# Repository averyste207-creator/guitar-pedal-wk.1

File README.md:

# Distortion Pedal

A DIY guitar distortion pedal project. This repository contains the circuit schematic and can be used to document the design, build process, testing, and future revisions.

## Circuit Schematic

## Overview

The schematic shows an analog distortion circuit built around an **LM741 operational amplifier**, with diode-clipping stages and adjustable controls.

- **Input:** Guitar signal input
- **Amplifier:** LM741 op-amp stage
- **Clipping:** Diodes provide signal clipping for distortion
- **Controls:** Potentiometers for adjusting the circuit response
- **Power:** 9 V supply is shown in the schematic
- **Output:** Distorted signal output

> This description is based on the current schematic. Confirm component values, pin connections, and power requirements before building the circuit.

## Components

The schematic includes the following parts (check the drawing and your chosen component footprints before ordering):

- LM741 operational amplifier
- 1N34A and 1N4148 diodes
- Resistors and capacitors as labeled in the schematic
- Potentiometers RV1 and RV2
- Input and output jacks
- 9 V power connection
- Breadboard or suitable PCB, hookup wire, and enclosure hardware

## Build Notes

1. Verify the schematic and component values.
2. Assemble the circuit on a breadboard before making a permanent PCB.
3. Check the power and ground connections before applying power.
4. Test with a low-volume amplifier setting first, then adjust the controls.
5. Record any changes to component values or wiring in this README.

## Project Status

**Status:** Schematic / prototype stage.

Build instructions, audio samples, enclosure details, and PCB files can be added as the project develops.

## Safety and Disclaimer

This is a low-voltage electronics project, but incorrect wiring can damage components or connected equipment. Double-check the power polarity and op-amp pinout before powering the circuit.

## License

No license has been specified yet. Add a `LICENSE` file if you want to define how others may use, modify, and distribute this project.

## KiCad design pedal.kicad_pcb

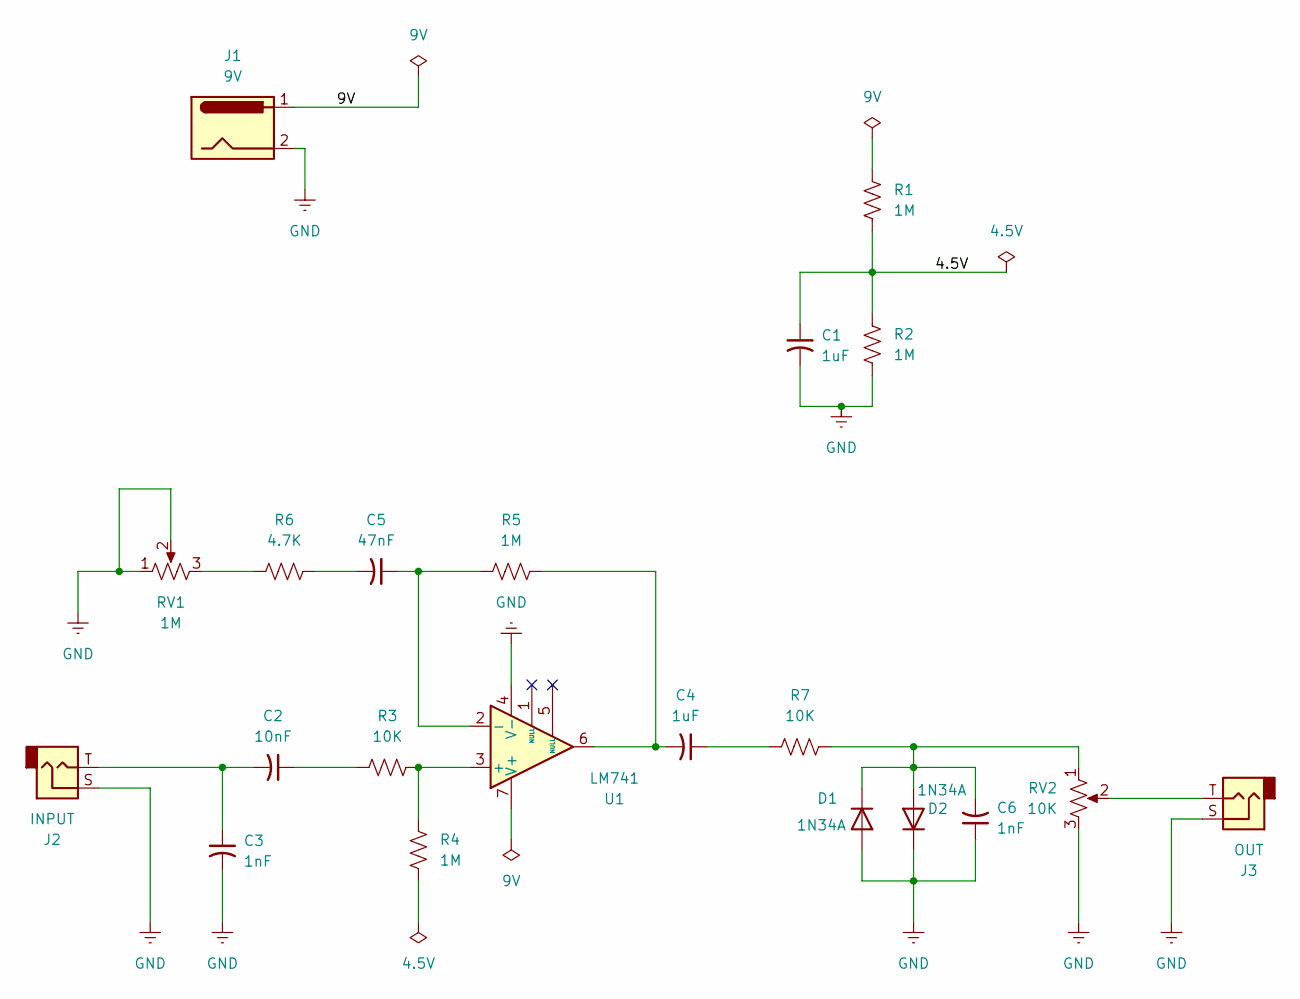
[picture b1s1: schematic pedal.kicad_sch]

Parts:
C1, C4: 1uF; CP_Radial_D4.0mm_P1.50mm
C2: 10nF; CP_Radial_D4.0mm_P1.50mm
C3, C6: 1nF; CP_Radial_D4.0mm_P1.50mm
C5: 47nF; CP_Radial_D4.0mm_P1.50mm
D1, D2: 1N34A; D_DO-35_SOD27_P7.62mm_Horizontal
J1: 9V; BarrelJack_Wuerth_694108106102_2.5x5.5mm
J2: INPUT; Jack_6.35mm_Neutrik_NMJ4HCD2_Horizontal
J3: OUT; Jack_6.35mm_Neutrik_NMJ4HCD2_Horizontal
R1, R2, R4, R5: 1M; R_Axial_DIN0204_L3.6mm_D1.6mm_P5.08mm_Horizontal
R3, R7: 10K; R_Axial_DIN0204_L3.6mm_D1.6mm_P5.08mm_Horizontal
R6: 4.7K; R_Axial_DIN0204_L3.6mm_D1.6mm_P5.08mm_Horizontal
RV1: 1M; Potentiometer_Bourns_PTV09A-1_Single_Vertical
RV2: 10K; Potentiometer_Bourns_PTV09A-1_Single_Vertical
U1: LM741; DIP-8_W7.62mm

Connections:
/4.5V: C1.1, R1.2, R2.1
/9V: J1.1
GND: C1.2, C3.2, C6.1, D1.2 (A), D2.1 (K), J1.2, J2.S, J3.S, R2.2, RV1.1, RV1.2, RV2.3, U1.4 (V-)
unnamed: C2.1, R3.1
unnamed: C2.2, C3.1, J2.T
unnamed: C4.1, R7.1
unnamed: C4.2, R5.2, U1.6
unnamed: C5.2, R6.2
unnamed: C6.2, D1.1 (K), D2.2 (A), R7.2, RV2.1
unnamed: J3.T, RV2.2
unnamed: R6.1, RV1.3
unnamed: R3.2, R4.2, U1.3 (+)
unnamed: C5.1, R5.1, U1.2 (-)

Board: 2 copper layers, 21 parts (0 on the bottom side), 12 nets, no tracks yet.
